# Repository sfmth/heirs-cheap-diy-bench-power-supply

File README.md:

## Heirs ANV-1030
Key features of this power supply are as follows:
- Cheap yet feature-rich variable DC-DC power supply
- Aimed towards beginners as a DIY electronics project
- Comprehensive documentation 
- Adequate accuracy and performance for general electronics use
- Use of cost oriented and widely available components
- A linear topology without digital control for simplicity and low cost
- Complete set of protections (OVP, OCP, OTP, SCP)

This variable analog bench power supply is designed whilst taking into consideration the following requirements:
- A relatively low power step-down DC-DC converter
- No digital control component
- Fast charge USB output with voltage and current monitoring outputs
- An Entirely non-switching linear topology
- Current, voltage, I_SET and OVP_SET should be displayable via two 3rd party voltmeter modules
- For visual output we are gonna use 3rd-party off-the-shelf voltmeter modules which can be priced as low as 0.90$ each
- Minimal over-shoot at power on/off
- Various protection mechanisms such as adjustable over-voltage(OVP), over-current(OCP), over-temperature(OTP), short-circuit(SCP), reverse voltage protection
- Remote voltage sensing (Kelvin wiring)
- Fan-less design relying on passive cooling
- Use of cost-oriented and widely available components
- Only a single variable output channel
- Modular design as the user can use any battery/ac-dc converter as the power source
- 

Wattmeter display
- OVP, CC, CV.  front panel LED
- front panel output on/off button

Add OCP

Use eeprom and adc for seven segment monitors

Goddammit adding stm8s003f3 cheapest microcontroller with an adc for front panel control

Now i have to reconsider a lot of things

Use pwm to drive output voltage through the opamp

Using pwm and adc at the same time might cause inaccuracies it should be tested for the specified microcontroller
 
 transformer tap for 220/110 compatibility
 
  beep on/off button
  
   standard distance between output terminals
   
   ovp ocp enable/disable button
   
   crow bar output protection
   
   soft and hard on/off switches
   
   ac input goes directly to the front panel
   
   different voltage taps of the transformer with relay or triac control for performance
   
   surviving fast shorts on the output
   
   gate being shorted to drain 
   
   thermally isolating the voltage reference on the pcb
   
   seethrough plexiglass front panel with laser print and cut
   
   پلکسی گلس خیابان پامنار
   
   mirror plexiglass reverse engraving
   
   main bjt transistors for durability
   
   electrophoresis compatible
   
   seperate digital and analog parts on the pcb

   seven segment display on the pcb

   optional switching pre regulator board for performance improvement
   
   analog programming of the power supply

   biocompatible with low leakage

   fast surge current protection for the load

   timer!

   kV surges from the output protection

  banana to usb converter

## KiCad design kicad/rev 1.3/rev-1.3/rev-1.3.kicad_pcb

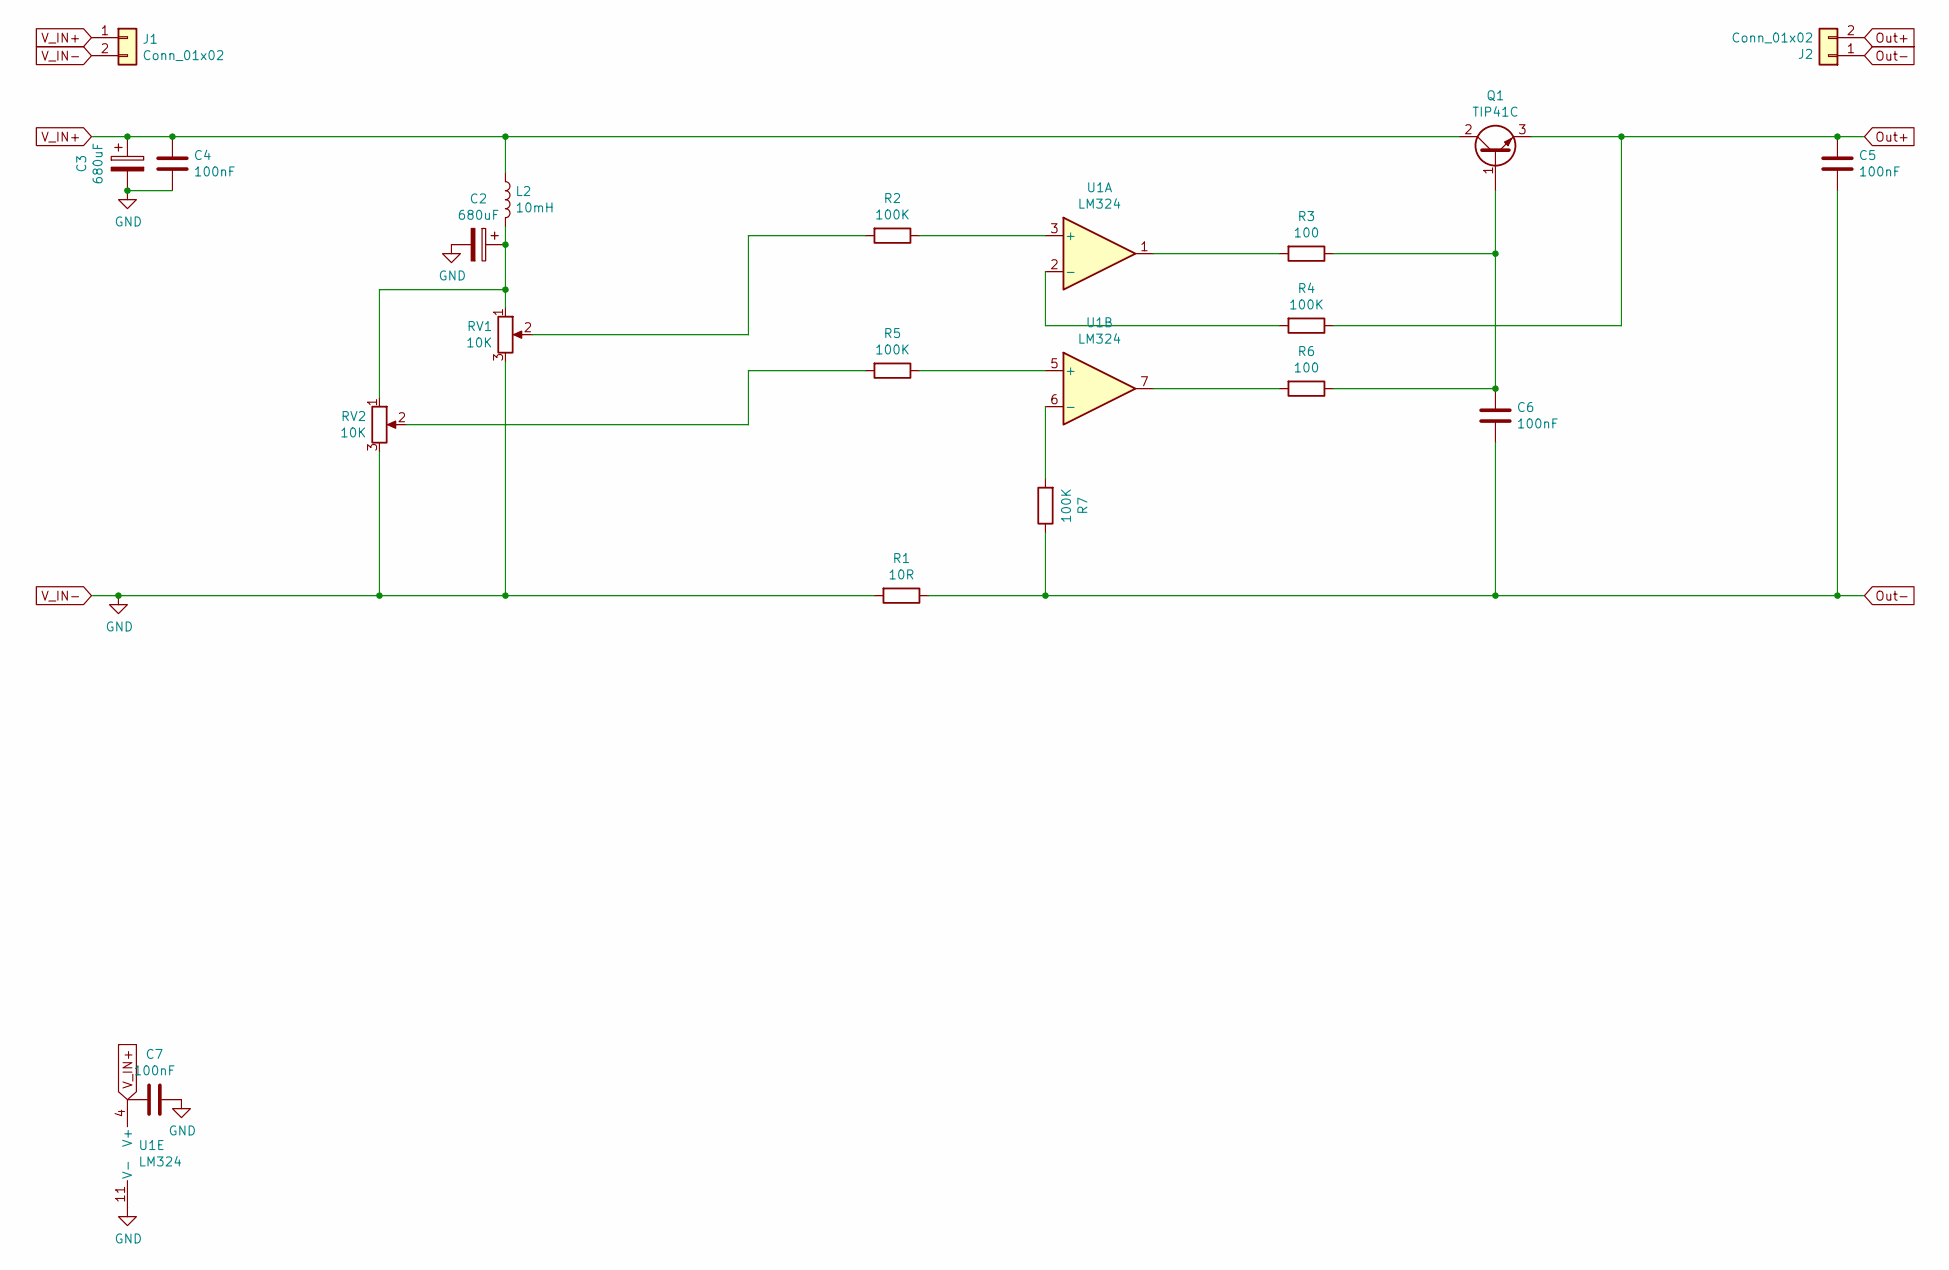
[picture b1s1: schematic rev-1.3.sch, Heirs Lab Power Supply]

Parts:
C2, C3: 680uF; CP_Radial_D8.0mm_P3.80mm
C4, C5, C6, C7: 100nF; C_Disc_D3.0mm_W1.6mm_P2.50mm
J1, J2: Conn_01x02; TerminalBlock_Altech_AK300-2_P5.00mm
L2: 10mH; L_Axial_L9.5mm_D4.0mm_P15.24mm_Horizontal_Fastron_SMCC
Q1: TIP41C; TO-220-3_Horizontal_TabDown
R1: 10R; R_Axial_DIN0309_L9.0mm_D3.2mm_P12.70mm_Horizontal
R2, R4, R5, R7: 100K; R_Axial_DIN0309_L9.0mm_D3.2mm_P12.70mm_Horizontal
R3, R6: 100; R_Axial_DIN0309_L9.0mm_D3.2mm_P12.70mm_Horizontal
RV1, RV2: 10K; Potentiometer_Piher_T-16L_Single_Vertical_Hole
U1: LM324; DIP-14_W7.62mm

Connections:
unnamed: C2.1, L2.2, RV1.1, RV2.1
unnamed: C6.2, Q1.1 (B), R3.1, R6.1
unnamed: R2.1, U1.3 (+)
unnamed: R2.2, RV1.2
unnamed: R3.2, U1.1
unnamed: R4.2, U1.2 (-)
unnamed: R5.1, U1.5 (+)
unnamed: R5.2, RV2.2
unnamed: R6.2, U1.7
unnamed: R7.2, U1.6 (-)
Out+: C5.2, J2.2, Q1.3 (E), R4.1
Out-: C5.1, C6.1, J2.1, R1.1, R7.1
V_IN+: C3.1, C4.2, C7.2, J1.1, L2.1, Q1.2 (C), U1.4 (V+)
V_IN-: C2.2, C3.2, C4.1, C7.1, J1.2, R1.2, RV1.3, RV2.3, U1.11 (V-)

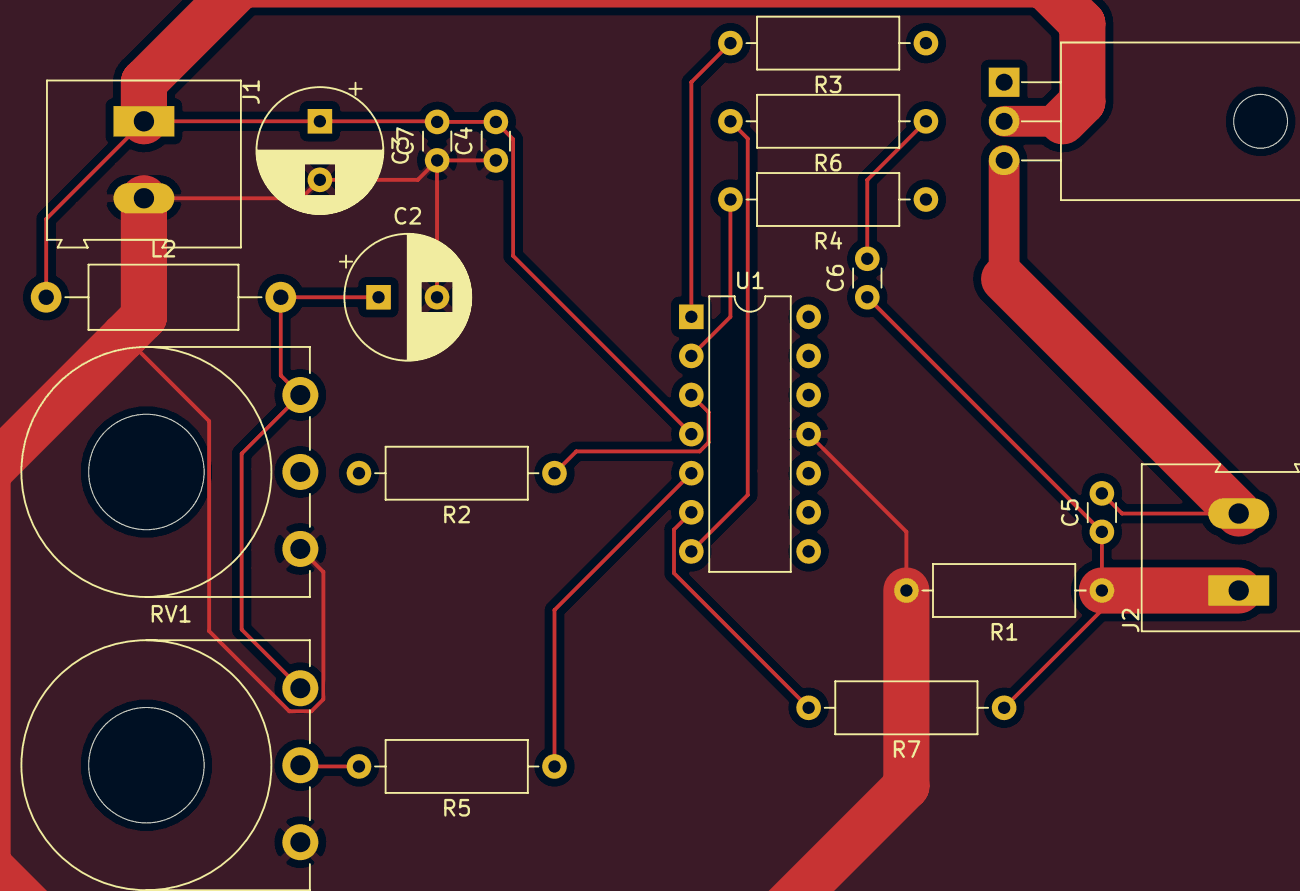
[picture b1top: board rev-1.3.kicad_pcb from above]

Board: 2 copper layers, 20 parts (0 on the bottom side), 14 nets.

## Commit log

2020-08-01 first prototype
2020-08-01 jjjjj
2020-08-03 jjjjjj
2020-08-03 Ffggg
2020-08-15 hdhdjdjdjdj
2020-08-18 dhhdhdb
2020-08-30 asfasf
2020-09-01 6/11
2021-03-21 banana to usb
2021-07-12 project briefing
